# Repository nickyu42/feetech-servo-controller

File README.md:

# feetech_servo_controller

Replacement controller board for Feetech FT6335M servos.  
For step response analysis, see: [controller.ipynb](./analysis/controller.ipynb).

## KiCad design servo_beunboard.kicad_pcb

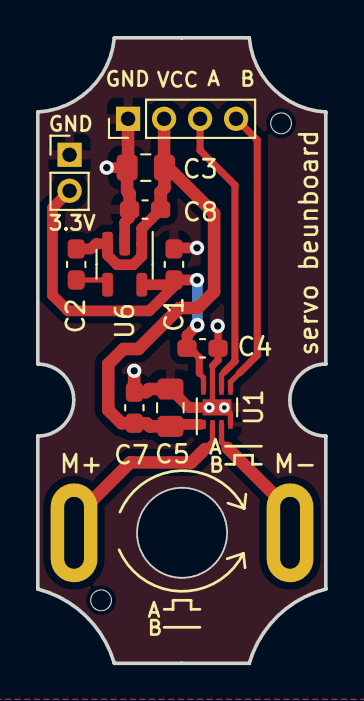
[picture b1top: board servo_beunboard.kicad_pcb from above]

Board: 2 copper layers, 16.0 x 34.8 mm, 14 parts (0 on the bottom side), 8 nets.

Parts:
C1, C8: 1uF; C_0603_1608Metric_Pad1.08x0.95mm_HandSolder
C2: 10nF; C_0603_1608Metric_Pad1.08x0.95mm_HandSolder
C3: 22uF; C_0805_2012Metric_Pad1.18x1.45mm_HandSolder
C4, C7: 100nF; C_0603_1608Metric_Pad1.08x0.95mm_HandSolder
C5: 10uF; C_0805_2012Metric_Pad1.18x1.45mm_HandSolder
H1, H2: MountingHole; JLC_ToolingHole
J1: ANGLE_SENSOR; PinHeader_1x02_P2.00mm_Vertical
J2: SERVO_INPUT; PinHeader_1x04_P2.00mm_Vertical
M1: Motor_DC; MOTOR_RK-130SH
U1: DRV8212DSG; WSON-8-1EP_2x2mm_P0.5mm_EP0.9x1.6mm
U6: SPX5205M5-L-3.3; SOT-23-5

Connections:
+3.3V: C1.1, C4.2, J1.2, U1.8 (VCC), U6.5 (VOUT)
/MOTOR_A: J2.3, U1.6 (IN1/PH)
/MOTOR_B: J2.4, U1.5 (IN2/EN)
GND: C1.2, C3.1, C4.1, C5.1, C7.1, C8.2, J1.1, J2.1, U1.4 (GND), U1.7 (MODE), U1.9 (EP), U6.2 (GND)
unnamed: M1.1 (+), U1.2 (OUT1)
unnamed: M1.2 (-), U1.3 (OUT2)
unnamed: C2.2, U6.4 (BYP)
VCC: C2.1, C3.2, C5.2, C7.2, C8.1, J2.2, U1.1 (VM), U6.1 (VIN), U6.3 (EN)

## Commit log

2023-05-01 Change LDO JLC part
2023-05-01 Enlarge motor pin holes
2023-05-05 Add controller.ipynb
